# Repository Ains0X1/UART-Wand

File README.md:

**UART-wand** 

It is an open-source, ultra-compact USB-to-Serial converter. It uses the CH340E IC to provide a stable asynchronous serial interface (UART) via a USB-C connector.

This design is ideal for developers working with ESP8266, ESP32, Arduino Pro Mini, or any system requiring a serial console where space is limited.

**Features**

USB-C Interface: Modern reversible connector for easy connectivity.

CH340E Chipset: No external crystal required, allowing for a tiny PCB footprint.

Compact Design: Dongle-style form factor that plugs directly into your computer.

Enhanced Reliability: Includes teardrops on all pads and vias for improved mechanical and electrical durability.

Standard Pinout: Breaks out TX, RX, VCC (5V/3.3V), and GND.

**Hardware Specifications**

PCB Layers: 2

Track Width: 0.2 mm

Minimum Clearance: 0.2 mm

Via Size: 0.6 mm (0.3 mm drill)

EDA Tool: KiCad 8.0+

**Getting Started**

Manufacturing: Use the provided KiCad files to generate Gerbers or use the provided BOM to order components.

Drivers: The CH340 chip is natively supported by most Linux distributions and macOS. For Windows, you may need to install the standard CH340 drivers.

Usage: Connect the TX/RX pins to your target device (cross-connect: TX to RX, RX to TX).

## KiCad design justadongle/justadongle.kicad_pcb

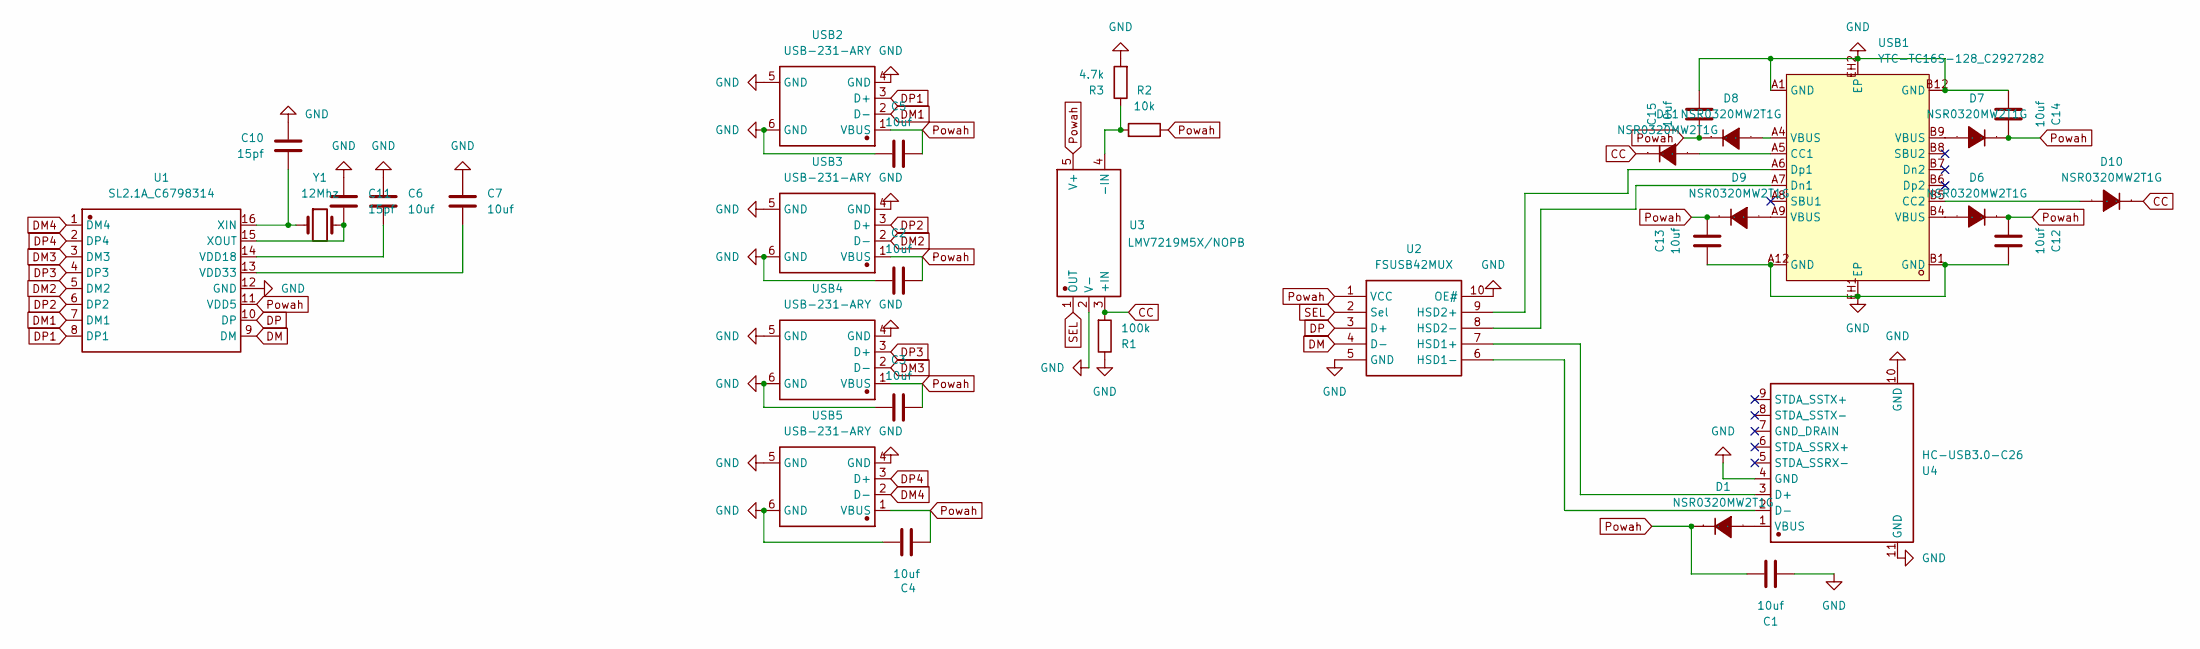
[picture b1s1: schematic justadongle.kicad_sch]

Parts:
C1, C2, C3, C4, C5, C6, C7, C12, C13, C14, C15: 10uf; C0805
C10, C11: 15pf; CAP-TH_BD5.0-P2.00-D0.8-FD
D1, D6, D7, D8, D9, D10, D11: NSR0320MW2T1G; SOD-323_L1.8-W1.3-LS2.5-RD; Manufacturer Part NSR0320MW2T1G
R1: 100k; RES-TH_BD2.4-L6.3-P10.30-D0.6
R2: 10k; RES-TH_BD2.4-L6.3-P10.30-D0.6
R3: 4.7k; RES-TH_BD2.4-L6.3-P10.30-D0.6
U1: SL2.1A_C6798314; SOP-16_L10.0-W3.9-P1.27-LS6.0-BL; Manufacturer Part SL2.1A
U2: FSUSB42MUX; MSOP-10_L3.0-W3.0-P0.50-LS5.0-BL; Manufacturer Part FSUSB42MUX
U3: LMV7219M5X/NOPB; SOT-23-5_L3.0-W1.7-P0.95-LS2.8-BR; Manufacturer Part LMV7219M5X/NOPB
U4: HC-USB3.0-C26; USB-3.0-A-SMD_HC-USB3.0-C26; Manufacturer Part HC-USB3.0-C26
USB1: YTC-TC16S-128_C2927282; TYPE-C-SMD_YTC-TC16S-128; LCSC Part C2927282
USB2, USB3, USB4, USB5: USB-231-ARY; USB-A-TH_USB-231-ARY; Manufacturer Part USB-231-ARY
Y1: 12Mhz; CAP-TH_BD5.0-P2.00-D0.8-FD

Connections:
CC: D10.1 (C), D11.1 (C), R1.2, U3.3 (+IN)
DM1: U1.7 (DM1), USB2.2 (D-)
DM2: U1.5 (DM2), USB3.2 (D-)
DM3: U1.3 (DM3), USB4.2 (D-)
DM4: U1.1 (DM4), USB5.2 (D-)
DM: U1.9 (DM), U2.4 (D-)
DP: U1.10 (DP), U2.3 (D+)
DP1: U1.8 (DP1), USB2.3 (D+)
DP2: U1.6 (DP2), USB3.3 (D+)
DP3: U1.4 (DP3), USB4.3 (D+)
DP4: U1.2 (DP4), USB5.3 (D+)
GND: C1.1, C2.1, C3.1, C4.1, C5.1, C6.1, C7.1, C10.1, C11.1, C12.2, C13.1, C14.1, C15.2, R1.1, R3.2, U1.12 (GND), U2.5 (GND), U2.10 (OE#), U3.2 (V-), U4.4 (GND), U4.10 (GND), U4.11 (GND), USB1.A1 (GND), USB1.A12 (GND), USB1.B1 (GND), USB1.B12 (GND), USB1.EH1 (EP), USB1.EH2 (EP), USB2.4 (GND), USB2.5 (GND), USB2.6 (GND), USB3.4 (GND), USB3.5 (GND), USB3.6 (GND), USB4.4 (GND), USB4.5 (GND), USB4.6 (GND), USB5.4 (GND), USB5.5 (GND), USB5.6 (GND)
unnamed: D1.2 (A), U4.1 (VBUS)
unnamed: D6.2 (A), USB1.B4 (VBUS)
unnamed: D7.2 (A), USB1.B9 (VBUS)
unnamed: D8.2 (A), USB1.A4 (VBUS)
unnamed: D9.2 (A), USB1.A9 (VBUS)
unnamed: D10.2 (A), USB1.B5 (CC2)
unnamed: D11.2 (A), USB1.A5 (CC1)
unnamed: C6.2, U1.14 (VDD18)
unnamed: C7.2, U1.13 (VDD33)
unnamed: C10.2, U1.16 (XIN), Y1.1
unnamed: C11.2, U1.15 (XOUT), Y1.2
unnamed: U2.7 (HSD1+), U4.3 (D+)
unnamed: U2.6 (HSD1-), U4.2 (D-)
unnamed: U2.9 (HSD2+), USB1.A6 (Dp1)
unnamed: U2.8 (HSD2-), USB1.A7 (Dn1)
unnamed: R2.2, R3.1, U3.4 (-IN)
Powah: C1.2, C2.2, C3.2, C4.2, C5.2, C12.1, C13.2, C14.2, C15.1, D1.1 (C), D6.1 (C), D7.1 (C), D8.1 (C), D9.1 (C), R2.1, U1.11 (VDD5), U2.1 (VCC), U3.5 (V+), USB2.1 (VBUS), USB3.1 (VBUS), USB4.1 (VBUS), USB5.1 (VBUS)
SEL: U2.2 (Sel), U3.1 (OUT)

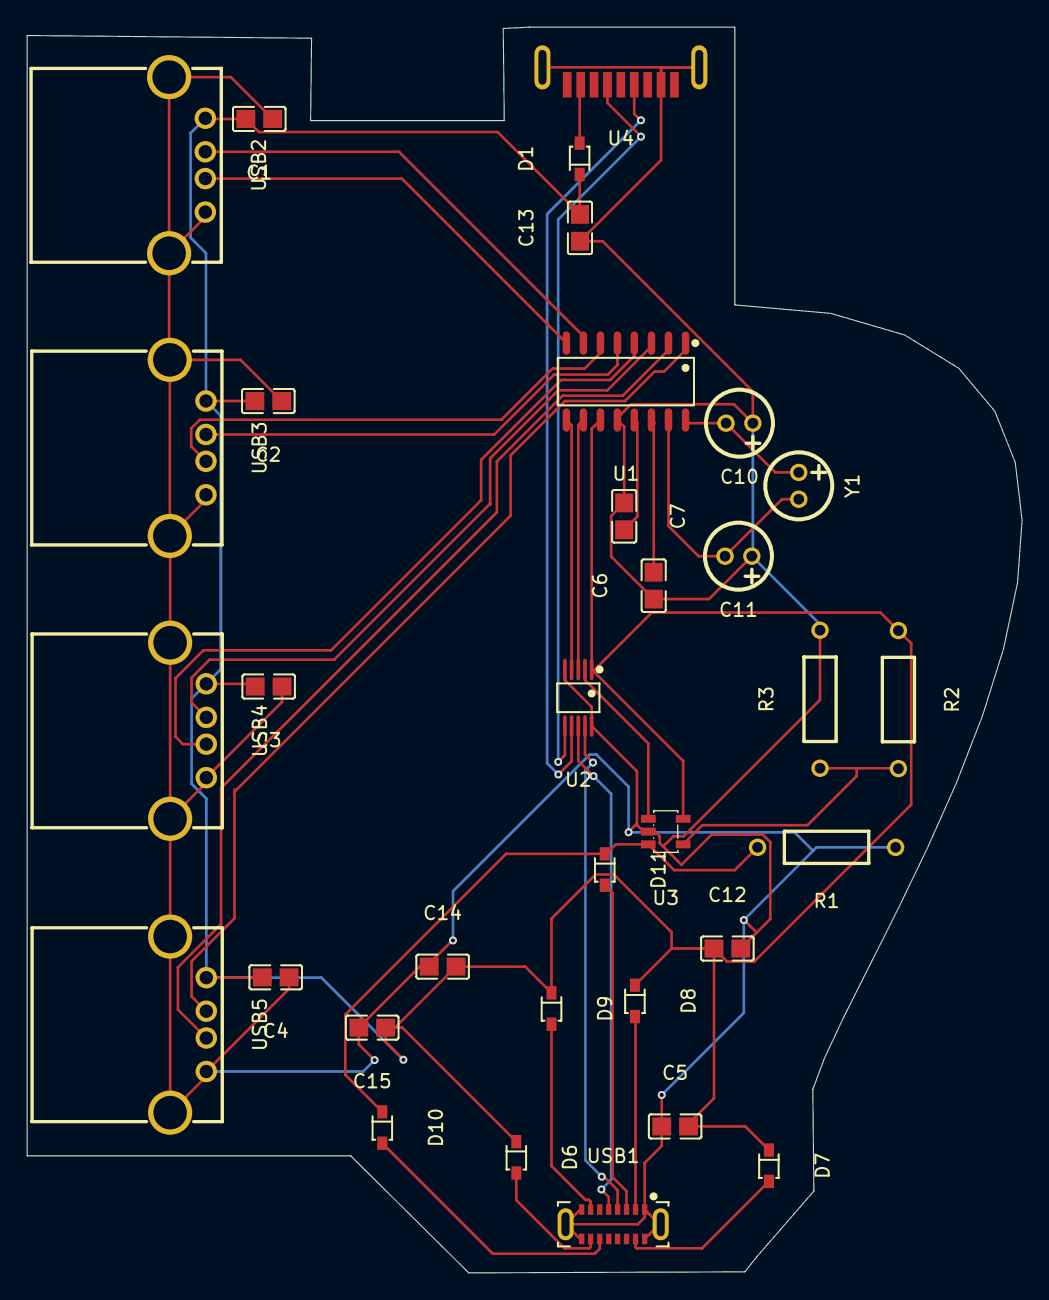
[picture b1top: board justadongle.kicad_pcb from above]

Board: 2 copper layers, 74.2 x 92.9 mm, 33 parts (0 on the bottom side), 30 nets.

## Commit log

2026-04-19 Add README for UART-wand project
    Added detailed information about UART-wand including features, hardware specifications, and getting started guide.
2026-04-19 Fix formatting in README.md
    Removed extra slashes and added spacing for clarity.
